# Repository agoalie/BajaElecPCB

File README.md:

# BajaElecPCB

Every PCB the Queen's Baja electrical team designs this year, one folder per board.

| Board | What it is |
|---|---|
| [`Baja2027_RPM`](Baja2027_RPM) | RPM sensor board |

All boards use KiCad 10. A file saved in KiCad 10 won't open in an older version.

## Getting started

```sh
git clone https://github.com/agoalie/BajaElecPCB.git
```

Clone it somewhere outside OneDrive or SharePoint. Sync tools can corrupt a `.git` folder.

## Daily workflow

Each board gets its own branch while it's being designed, such as `daq`. Small fixes to a
finished board can use a short branch, such as `rpm/move-connector`.

1. Update first: `git switch main && git pull`
2. Branch: `git switch -c daq`
3. Make your change in KiCad and save.
4. See what changed: `python3 tools/pcbdiff.py Baja2027_DAQ --open`
5. Commit and push: `git add Baja2027_DAQ && git commit -m "DAQ: add CAN transceiver" && git push -u origin HEAD`
6. Open a pull request early, with a title like `WIP: DAQ board`. Before asking for a
   review, run ERC and DRC in KiCad, with DRC's option to test the PCB against the schematic.
7. Merge at each milestone: once the schematic has been reviewed, and again when the layout
   has been reviewed and is ready to order.

**Only one person should edit a given `.kicad_pcb` or `.kicad_sch` at a time.** Git can't
merge these files. If two people change the same one, Git reports a conflict, and one of
them has to redo their work on top of the other's version. Say who's working on which
board before you start. Separate schematic sheets can be edited by different people.

**A modified `.kicad_pcb` doesn't always mean the design changed.** KiCad can reorder a
file's contents when it saves, which shows up as hundreds of changed lines. Run
`pcbdiff.py` to see whether anything real changed.

## Tagging what you order

When a board goes to fabrication, export it, merge to `main`, and tag that commit:

```sh
git switch main && git pull
git tag rpm-v1.1
git push origin rpm-v1.1
```

Name tags `<board>-v<version>` and use the same version on the silkscreen. Use a new version
for each physically different board, and don't move a tag once that board has been ordered.
To see what has changed since an order, run `python3 tools/pcbdiff.py Baja2027_RPM rpm-v1.0 --open`.

## Tools

All of these need Python 3 and KiCad, and nothing else.

### See a visual diff: `tools/pcbdiff.py`

```sh
python3 tools/pcbdiff.py Baja2027_RPM                # last commit vs. your working folder
python3 tools/pcbdiff.py Baja2027_RPM main --open    # main vs. your work, opened in the browser
python3 tools/pcbdiff.py Baja2027_RPM HEAD~3 HEAD    # any two versions
```

This builds `pcbdiff-out/<board>/index.html`, which has:

- **Every schematic sheet and PCB layer**, with changed ones marked by a dot.
- **Three views:** overlay (red removed, green added), side by side, and a swipe slider.
  Scroll to zoom and drag to pan.
- **A change list:** components added, removed, or edited, net connections that changed,
  and footprints that moved.

### Export for JLCPCB: `tools/kicad_jlc_export.py`

```sh
python3 tools/kicad_jlc_export.py Baja2027_RPM
```

Writes the gerber and drill zip, BOM, and CPL to `<board>/jlc_export/`. Rotation fixes
found in JLCPCB's preview go in `<board>/jlc_export.json`. This is the only fabrication
output to commit, so re-run it and commit the result before ordering. Don't commit exports
from KiCad's plot or BOM windows, because they go stale.

If you'd rather not use the command line, [GitHub Desktop](https://desktop.github.com/)
works with this repo. Add `BajaElecPCB` as a local repository. KiCad's built-in Git menu
may not appear here, because each project sits one folder below the repo root.

## Adding a board

1. Create the project in its own top-level folder, such as `Baja2027_DAQ/`, with exactly
   one `.kicad_pro`.
2. Keep project-specific footprints in `<board>/Library.pretty` and 3D models in
   `<board>/3dmodels`, referenced through `${KIPRJMOD}`, so the board works on any computer.
3. Open and save it in KiCad 10 once, then commit before making real changes. This stops
   a later save from reordering the whole file, which matters most for a board started
   elsewhere or in an older version.
4. Add it to the table above.

## What's tracked

**Tracked:** schematics, PCB, project and rule files, local libraries, part 3D models, and
`jlc_export/`.

**Ignored:** KiCad backups and local history, per-user `.kicad_prl` files, caches, and
whole-board STEP exports. Regenerate STEP files with **File → Export → STEP**. GitHub
rejects any file over 100 MB, so keep part models small.

## Shared library

Some footprints and 3D models come from the team library on SharePoint, through the
`SHAREPOINT_LIB` path variable in KiCad (**Preferences → Configure Paths**). Point it at
your synced copy of `2027/Design/Electrical/KiCAD`. Without it, those parts' 3D models
won't appear, but the schematic, layout, and these tools still work.

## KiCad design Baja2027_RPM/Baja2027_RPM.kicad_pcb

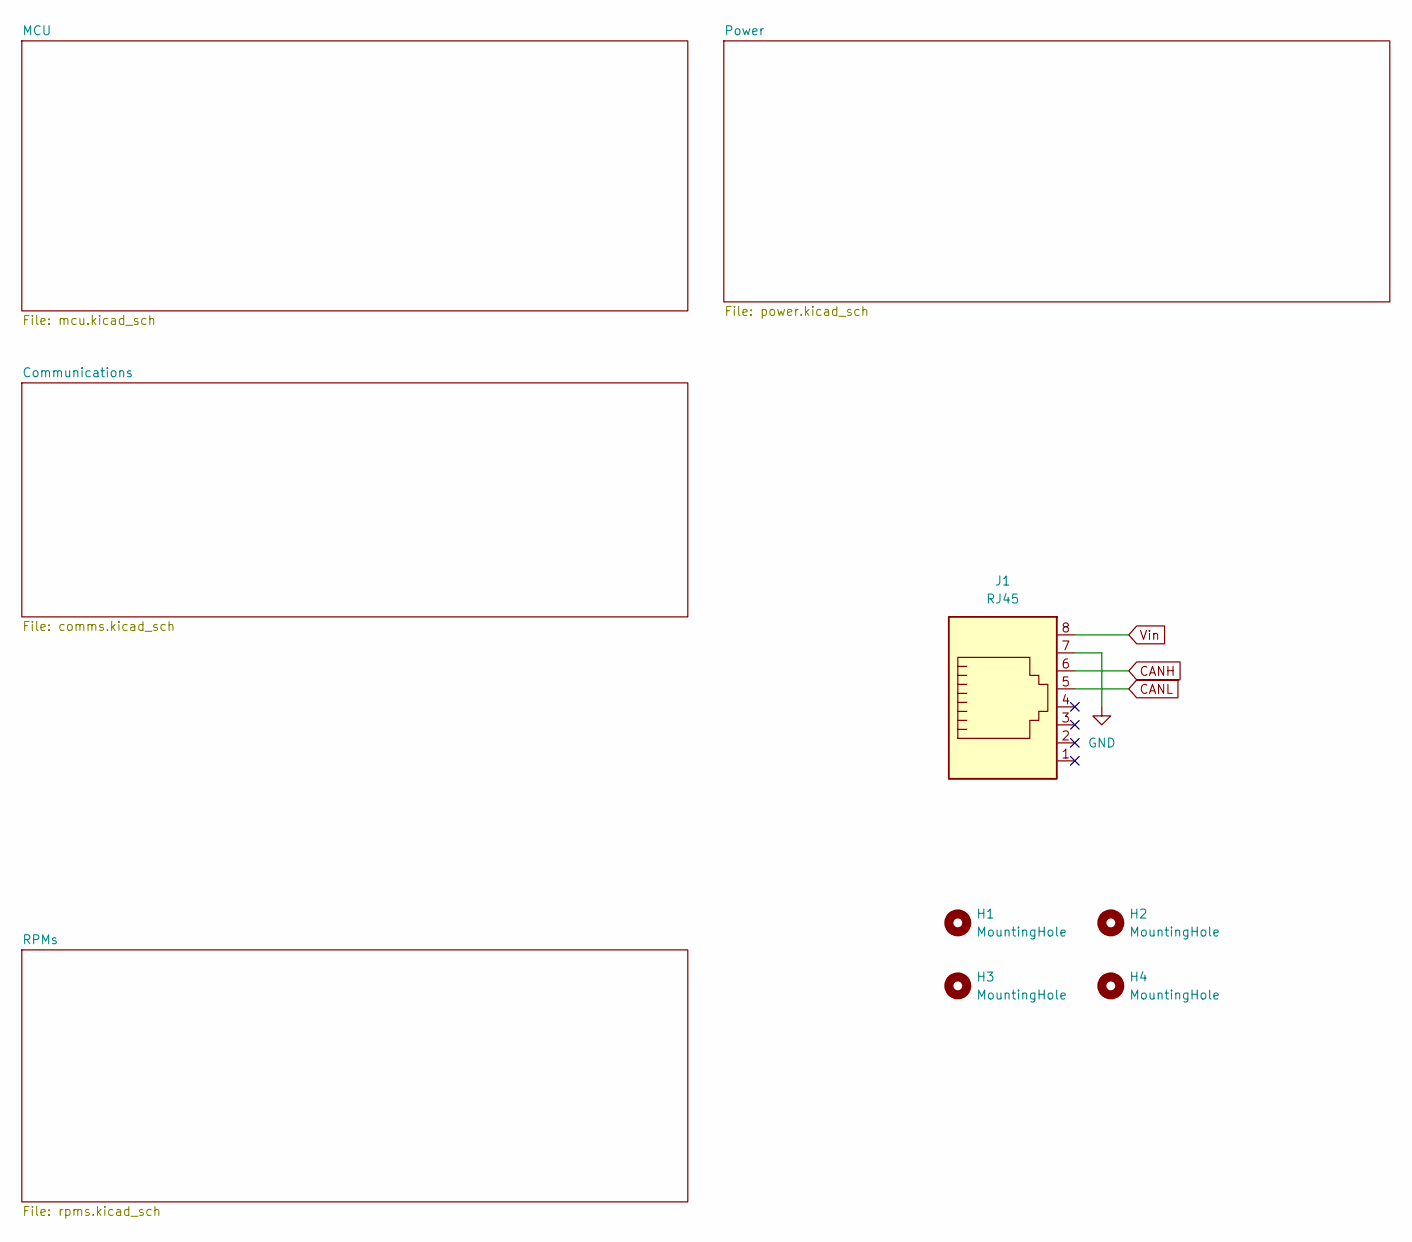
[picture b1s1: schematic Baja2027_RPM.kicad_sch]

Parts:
H1, H2, H3, H4: MountingHole; MountingHole_4.3mm_M4
J1: RJ45; LCSC PART # C385834

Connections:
CANH: J1.6; also elsewhere on the board
CANL: J1.5; also elsewhere on the board
GND: J1.7; also elsewhere on the board
Vin: J1.8; also elsewhere on the board

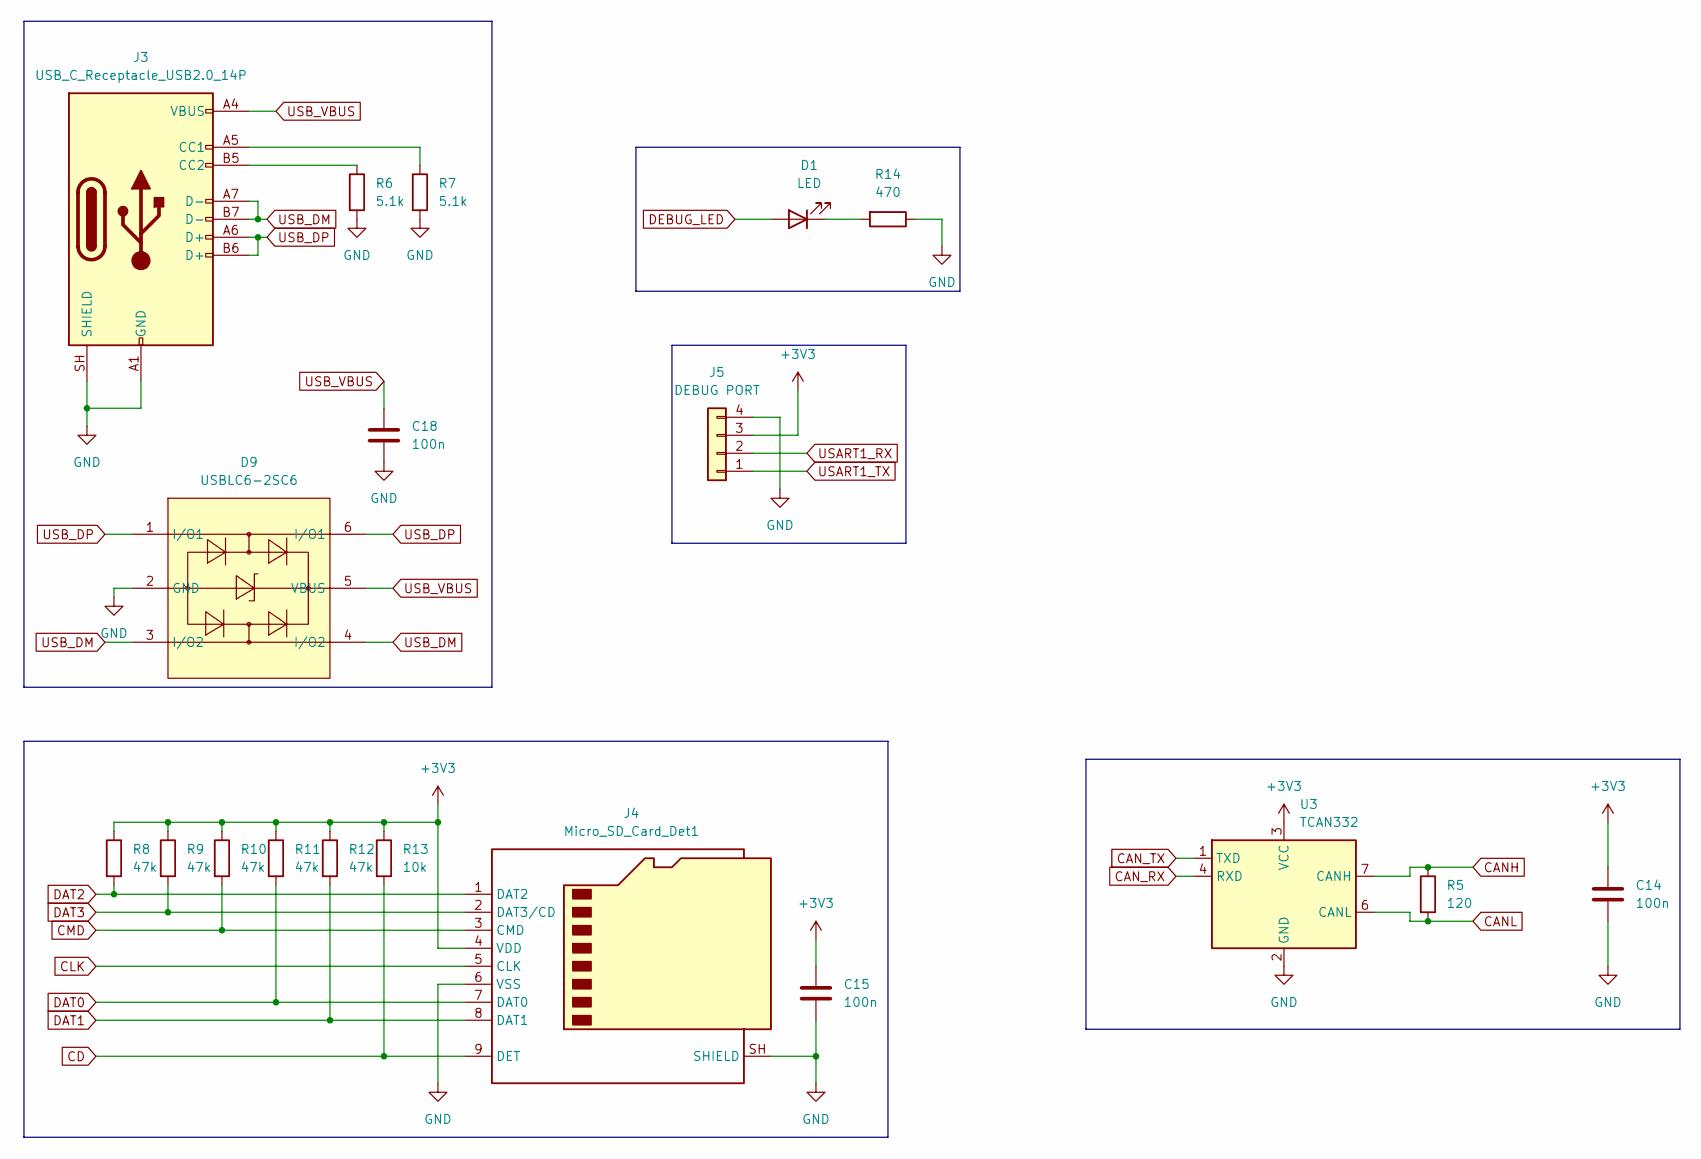
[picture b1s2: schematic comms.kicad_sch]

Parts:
C14, C15, C18: 100n; C_0402_1005Metric; LCSC PART # C1525
D1: LED; LED_0603_1608Metric; LCSC PART # C2286
D9: USBLC6-2SC6; MPN USBLC6-2SC6; LCSC PART # C7519
J3: USB_C_Receptacle_USB2.0_14P; USB_C_Receptacle_GCT_USB4105-xx-A_16P_TopMnt_Horizontal; LCSC PART # C2765186
J4: Micro_SD_Card_Det1; Sd Card Slot; LCSC PART # C91145
J5: DEBUG PORT; PinHeader_1x04_P2.54mm_Vertical; LCSC PART # C32713270
R5: 120; R_0402_1005Metric; LCSC PART # C25079
R6, R7: 5.1k; R_0402_1005Metric; LCSC PART # C25905
R8, R9, R10, R11, R12: 47k; R_0402_1005Metric; LCSC PART # C25792
R13: 10k; R_0402_1005Metric; LCSC PART # C25744
R14: 470; R_0402_1005Metric; LCSC PART # C25117
U3: TCAN332; LCSC PART # C2671083

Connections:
+3V3: C14.1, C15.1, J4.4 (VDD), J5.3, R8.1, R9.1, R10.1, R11.1, R12.1, R13.1, U3.3 (VCC); also elsewhere on the board
CANH: R5.1, U3.7 (CANH); also elsewhere on the board
CANL: R5.2, U3.6 (CANL); also elsewhere on the board
CAN_RX: U3.4 (RXD); also elsewhere on the board
CAN_TX: U3.1 (TXD); also elsewhere on the board
CD: J4.9 (DET), R13.2; also elsewhere on the board
CLK: J4.5 (CLK); also elsewhere on the board
CMD: J4.3 (CMD), R10.2; also elsewhere on the board
DAT0: J4.7 (DAT0), R11.2; also elsewhere on the board
DAT1: J4.8 (DAT1), R12.2; also elsewhere on the board
DAT2: J4.1 (DAT2), R8.2; also elsewhere on the board
DAT3: J4.2 (DAT3/CD), R9.2; also elsewhere on the board
DEBUG_LED: D1.2 (A); also elsewhere on the board
GND: C14.2, C15.2, C18.1, D9.2 (GND), J3.A1 (GND), J3.A12 (GND), J3.B1 (GND), J3.B12 (GND), J3.SH (SHIELD), J4.6 (VSS), J4.SH (SHIELD), J5.4, R6.2, R7.2, R14.1, U3.2 (GND); also elsewhere on the board
unnamed: D1.1 (K), R14.2
unnamed: J3.A5 (CC1), R7.1
unnamed: J3.B5 (CC2), R6.1
USART1_RX: J5.2; also elsewhere on the board
USART1_TX: J5.1; also elsewhere on the board
USB_DM: D9.3 (I/O2), D9.4 (I/O2), J3.A7 (D-), J3.B7 (D-); also elsewhere on the board
USB_DP: D9.1 (I/O1), D9.6 (I/O1), J3.A6 (D+), J3.B6 (D+); also elsewhere on the board
USB_VBUS: C18.2, D9.5 (VBUS), J3.A4 (VBUS), J3.A9 (VBUS), J3.B4 (VBUS), J3.B9 (VBUS); also elsewhere on the board

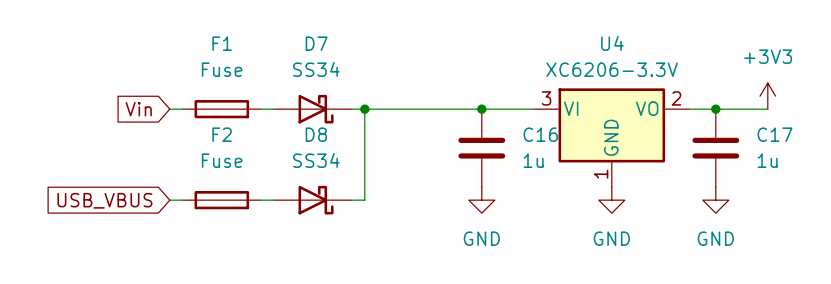
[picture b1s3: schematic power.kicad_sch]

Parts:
C16, C17: 1u; C_0402_1005Metric; LCSC PART # C52923
D7, D8: SS34; D_SMA; LCSC PART # C8678
F1, F2: Fuse; MF-NSMF050-2_Fuse; LCSC PART # C75464
U4: XC6206-3.3V; SOT-23-3; LCSC PART # C2891841

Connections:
+3V3: C17.1, U4.2 (VO); also elsewhere on the board
GND: C16.2, C17.2, U4.1 (GND); also elsewhere on the board
unnamed: D7.2 (A), F1.2
unnamed: C16.1, D7.1 (K), D8.1 (K), U4.3 (VI)
unnamed: D8.2 (A), F2.2
USB_VBUS: F2.1; also elsewhere on the board
Vin: F1.1; also elsewhere on the board

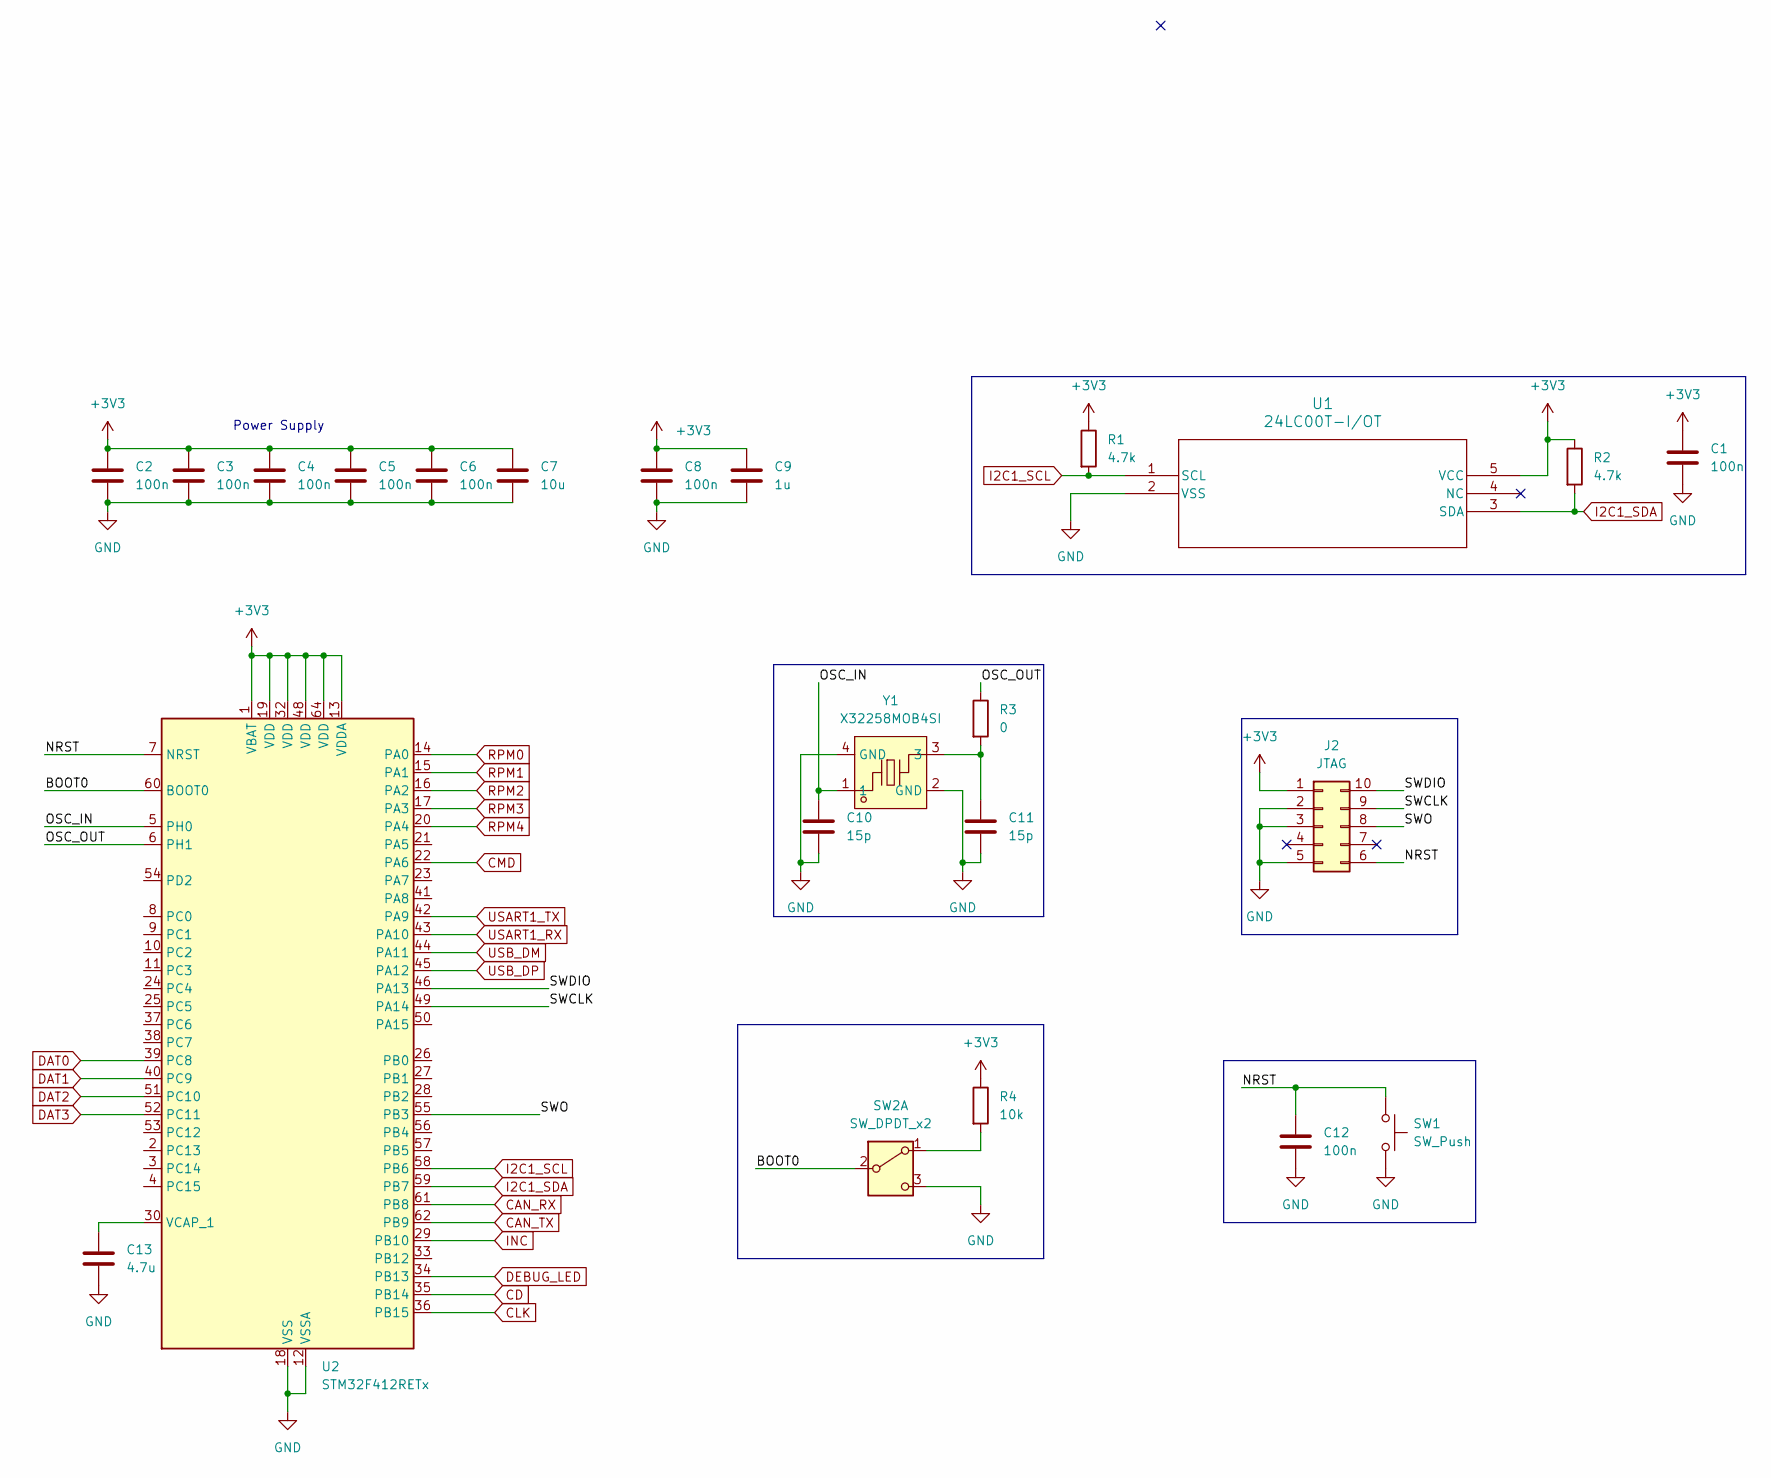
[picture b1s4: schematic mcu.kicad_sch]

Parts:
C1, C2, C3, C4, C5, C6, C8, C12: 100n; C_0402_1005Metric; LCSC PART # C1525
C7: 10u; C_0402_1005Metric; LCSC PART # C15525
C9: 1u; C_0402_1005Metric; LCSC PART # C52923
C10, C11: 15p; C_0402_1005Metric; LCSC PART # C1548
C13: 4.7u; C_0402_1005Metric; LCSC PART # C23733
J2: JTAG; LCSC PART # C2977596
R1, R2: 4.7k; R_0402_1005Metric; LCSC PART # C25900
R3: 0; R_0402_1005Metric; LCSC PART # C17168
R4: 10k; R_0402_1005Metric; LCSC PART # C25744
SW1: SW_Push; SW_Push_1P1T_XKB_TS-1187A; LCSC PART # C318884
SW2: SW_DPDT_x2; PinHeader_1x03_P2.54mm_Vertical; LCSC PART # C3337081
U1: 24LC00T-I/OT; 24LC00T_EEPROM_SOT-23-5_MC_MCH; LCSC PART # C2062024
U2: STM32F412RETx; LQFP-64_10x10mm_P0.5mm; LCSC PART # C89374
Y1: X32258MOB4SI; X32258MOB4SI_8MHz_Crystal; MPN X32258MOB4SI; LCSC Part C2682775

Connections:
+3V3: C1.1, C2.1, C3.1, C4.1, C5.1, C6.1, C7.1, C8.1, C9.1, J2.1, R1.1, R2.1, R4.1, U1.5 (VCC), U2.1 (VBAT), U2.13 (VDDA), U2.19 (VDD), U2.32 (VDD), U2.48 (VDD), U2.64 (VDD); also elsewhere on the board
/MCU/BOOT0: SW2.2 (B), U2.60 (BOOT0)
/MCU/NRST: C12.1, J2.6, SW1.1, U2.7 (NRST)
/MCU/OSC_IN: C10.1, U2.5 (PH0), Y1.1
/MCU/OSC_OUT: R3.1, U2.6 (PH1)
/MCU/SWCLK: J2.9, U2.49 (PA14)
/MCU/SWDIO: J2.10, U2.46 (PA13)
/MCU/SWO: J2.8, U2.55 (PB3)
CAN_RX: U2.61 (PB8); also elsewhere on the board
CAN_TX: U2.62 (PB9); also elsewhere on the board
CD: U2.35 (PB14); also elsewhere on the board
CLK: U2.36 (PB15); also elsewhere on the board
CMD: U2.22 (PA6); also elsewhere on the board
DAT0: U2.39 (PC8); also elsewhere on the board
DAT1: U2.40 (PC9); also elsewhere on the board
DAT2: U2.51 (PC10); also elsewhere on the board
DAT3: U2.52 (PC11); also elsewhere on the board
DEBUG_LED: U2.34 (PB13); also elsewhere on the board
GND: C1.2, C2.2, C3.2, C4.2, C5.2, C6.2, C7.2, C8.2, C9.2, C10.2, C11.2, C12.2, C13.2, J2.2, J2.3, J2.5, SW1.2, SW2.3 (C), U1.2 (VSS), U2.12 (VSSA), U2.18 (VSS), U2.31 (VSS), U2.47 (VSS), U2.63 (VSS), Y1.2 (GND), Y1.4 (GND); also elsewhere on the board
I2C1_SCL: R1.2, U1.1 (SCL), U2.58 (PB6)
I2C1_SDA: R2.2, U1.3 (SDA), U2.59 (PB7)
INC: U2.29 (PB10)
unnamed: C11.1, R3.2, Y1.3
unnamed: R4.2, SW2.1 (A)
unnamed: C13.1, U2.30 (VCAP_1)
RPM0: U2.14 (PA0); also elsewhere on the board
RPM1: U2.15 (PA1); also elsewhere on the board
RPM2: U2.16 (PA2); also elsewhere on the board
RPM3: U2.17 (PA3); also elsewhere on the board
RPM4: U2.20 (PA4); also elsewhere on the board
USART1_RX: U2.43 (PA10); also elsewhere on the board
USART1_TX: U2.42 (PA9); also elsewhere on the board
USB_DM: U2.44 (PA11); also elsewhere on the board
USB_DP: U2.45 (PA12); also elsewhere on the board

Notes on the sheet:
Power Supply

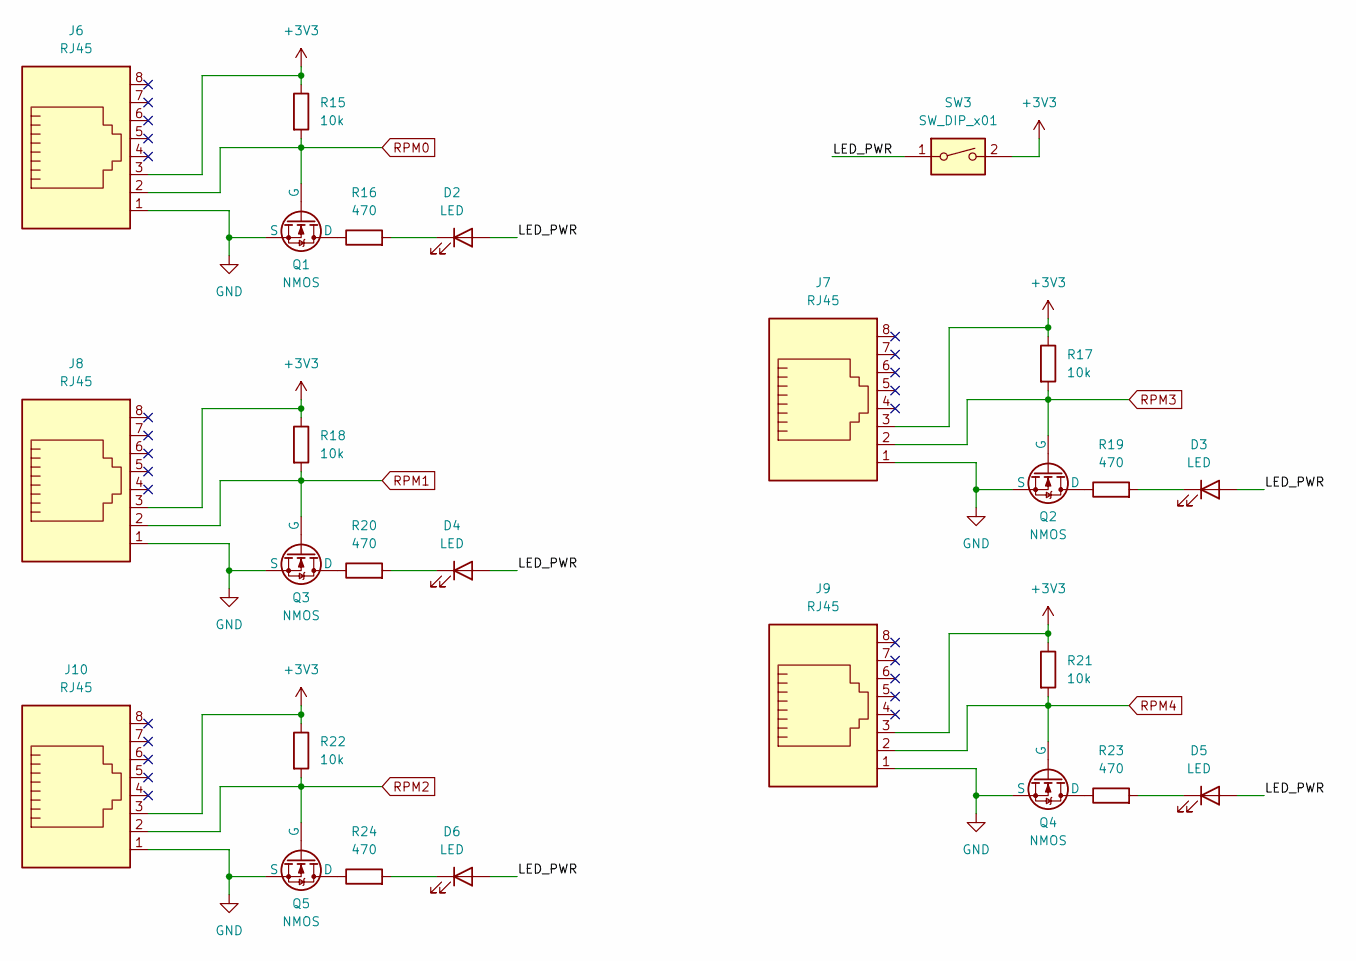
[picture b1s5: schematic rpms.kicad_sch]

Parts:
D2, D3, D4, D5, D6: LED; LED_0603_1608Metric; LCSC PART # C2286
J6, J7, J8, J9, J10: RJ45; LCSC PART # C385834
Q1, Q2, Q3, Q4, Q5: NMOS; SOT-23; Digikey Part Number 1727-4789-1-ND
R15, R17, R18, R21, R22: 10k; R_0402_1005Metric; LCSC PART # C25744
R16, R19, R20, R23, R24: 470; R_0402_1005Metric; LCSC PART # C25117
SW3: SW_DIP_x01; CHS-01TB_DIPSWITCH; LCSC PART # C2680613

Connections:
+3V3: J6.3, J7.3, J8.3, J9.3, J10.3, R15.1, R17.1, R18.1, R21.1, R22.1, SW3.2; also elsewhere on the board
/RPMs/LED_PWR: D2.2 (A), D3.2 (A), D4.2 (A), D5.2 (A), D6.2 (A), SW3.1
GND: J6.1, J7.1, J8.1, J9.1, J10.1, Q1.2 (S), Q2.2 (S), Q3.2 (S), Q4.2 (S), Q5.2 (S); also elsewhere on the board
unnamed: D2.1 (K), R16.2
unnamed: D3.1 (K), R19.2
unnamed: D4.1 (K), R20.2
unnamed: D5.1 (K), R23.2
unnamed: D6.1 (K), R24.2
unnamed: Q1.3 (D), R16.1
unnamed: Q2.3 (D), R19.1
unnamed: Q3.3 (D), R20.1
unnamed: Q4.3 (D), R23.1
unnamed: Q5.3 (D), R24.1
RPM0: J6.2, Q1.1 (G), R15.2; also elsewhere on the board
RPM1: J8.2, Q3.1 (G), R18.2; also elsewhere on the board
RPM2: J10.2, Q5.1 (G), R22.2; also elsewhere on the board
RPM3: J7.2, Q2.1 (G), R17.2; also elsewhere on the board
RPM4: J9.2, Q4.1 (G), R21.2; also elsewhere on the board

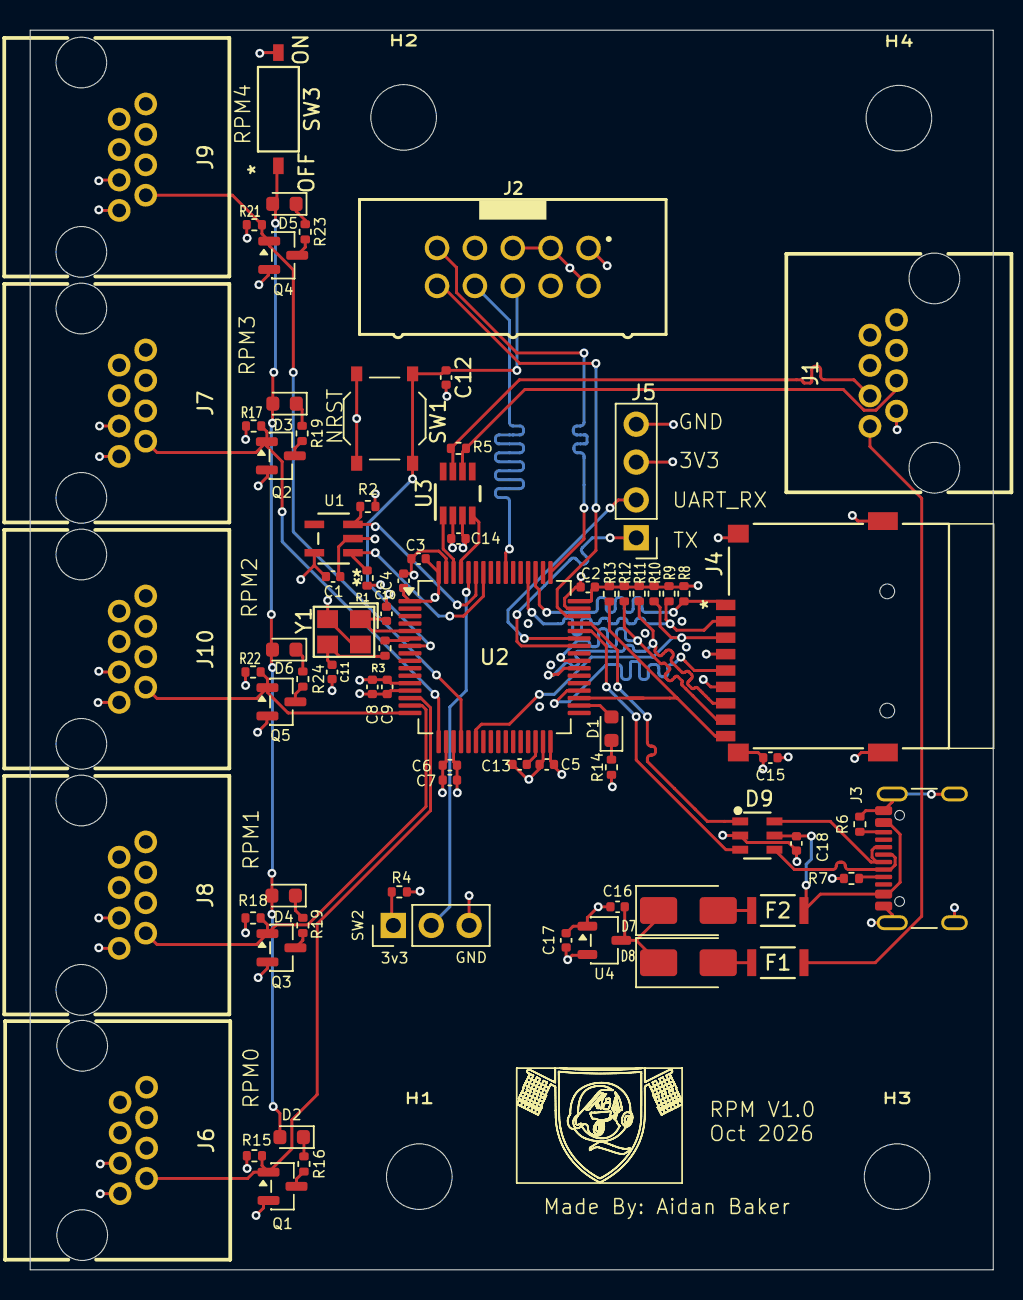
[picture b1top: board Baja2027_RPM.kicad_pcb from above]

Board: 4 copper layers, 64.6 x 83.1 mm, 80 parts (0 on the bottom side), 54 nets.

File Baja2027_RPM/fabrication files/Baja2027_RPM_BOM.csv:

Designator,Qty,Comment,LCSC PART #,Footprint
"C1,C2,C3,C4,C5,C6,C8,C12,C14,C15",10,100n,C1525,Capacitor_SMD:C_0402_1005Metric
C7,1,10u,C15525,Capacitor_SMD:C_0402_1005Metric
"C9,C16,C17",3,1u,C52923,Capacitor_SMD:C_0402_1005Metric
"C10,C11",2,15p,C1548,Capacitor_SMD:C_0402_1005Metric
C13,1,4.7u,C23733,Capacitor_SMD:C_0402_1005Metric
"D1,D2,D3,D4,D5,D6",6,LED,C2286,LED_SMD:LED_0603_1608Metric
"D7,D8",2,SS34,C8678,Diode_SMD:D_SMA
"F1,F2",2,Fuse,C75464,SHAREPOINT_Baja2027:MF-NSMF050-2_Fuse
"J1,J6,J7,J8,J9,J10",6,RJ45,C385834,SHAREPOINT_Baja2027:RJ45
J2,1,JTAG,C2977596,SHAREPOINT_Baja2027:JTAG
J3,1,USB_C_Receptacle_USB2.0_14P,C2765186,Connector_USB:USB_C_Receptacle_GCT_USB4105-xx-A_16P_TopMnt_Horizontal
J4,1,Micro_SD_Card_Det1,C91145,SHAREPOINT_Baja2027:Sd Card Slot
J5,1,DEBUG PORT,C32713270,Connector_PinHeader_2.54mm:PinHeader_1x04_P2.54mm_Vertical
"Q1,Q2,Q3,Q4,Q5",5,NMOS,C282405,Package_TO_SOT_SMD:SOT-23
"R1,R2",2,4.7k,C25900,Resistor_SMD:R_0402_1005Metric
R3,1,0,C17168,Resistor_SMD:R_0402_1005Metric
"R4,R13,R15,R17,R18,R21,R22",7,10k,C25744,Resistor_SMD:R_0402_1005Metric
R5,1,120,C25079,Resistor_SMD:R_0402_1005Metric
"R6,R7",2,5.1k,C25905,Resistor_SMD:R_0402_1005Metric
"R8,R9,R10,R11,R12",5,47k,C25792,Resistor_SMD:R_0402_1005Metric
"R14,R16,R19,R20,R23,R24",6,470,C25117,Resistor_SMD:R_0402_1005Metric
SW1,1,SW_Push,C318884,Button_Switch_SMD:SW_Push_1P1T_XKB_TS-1187A
SW2,1,SW_DPDT_x2,C3337081,Connector_PinHeader_2.54mm:PinHeader_1x03_P2.54mm_Vertical
SW3,1,SW_DIP_x01,C2680613,SHAREPOINT_Baja2027:CHS-01TB_DIPSWITCH
U1,1,24LC00T-I/OT,C2062024,SHAREPOINT_Baja2027:24LC00T_EEPROM_SOT-23-5_MC_MCH
U2,1,STM32F412RETx,STM32F412RETx,Package_QFP:LQFP-64_10x10mm_P0.5mm
U3,1,TCAN332,C2671083,CAN:TCAN332
U4,1,MCP1700x-330xxTT,C2891841,Package_TO_SOT_SMD:SOT-23-3
Y1,1,X32258MOB4SI,C2682775,SHAREPOINT_Baja2027:X32258MOB4SI_8MHz_Crystal
